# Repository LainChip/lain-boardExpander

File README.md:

# lain-boardExpander

NSCSCC 2023 Lain Core项目SoC使用的拓展板卡。

基于tyh学长的sd拓展板卡，删除了Type-C口，添加01x11排母用于连接PCM5102 I2S DAC。

原理图：

使用工具：KiCad 7.0

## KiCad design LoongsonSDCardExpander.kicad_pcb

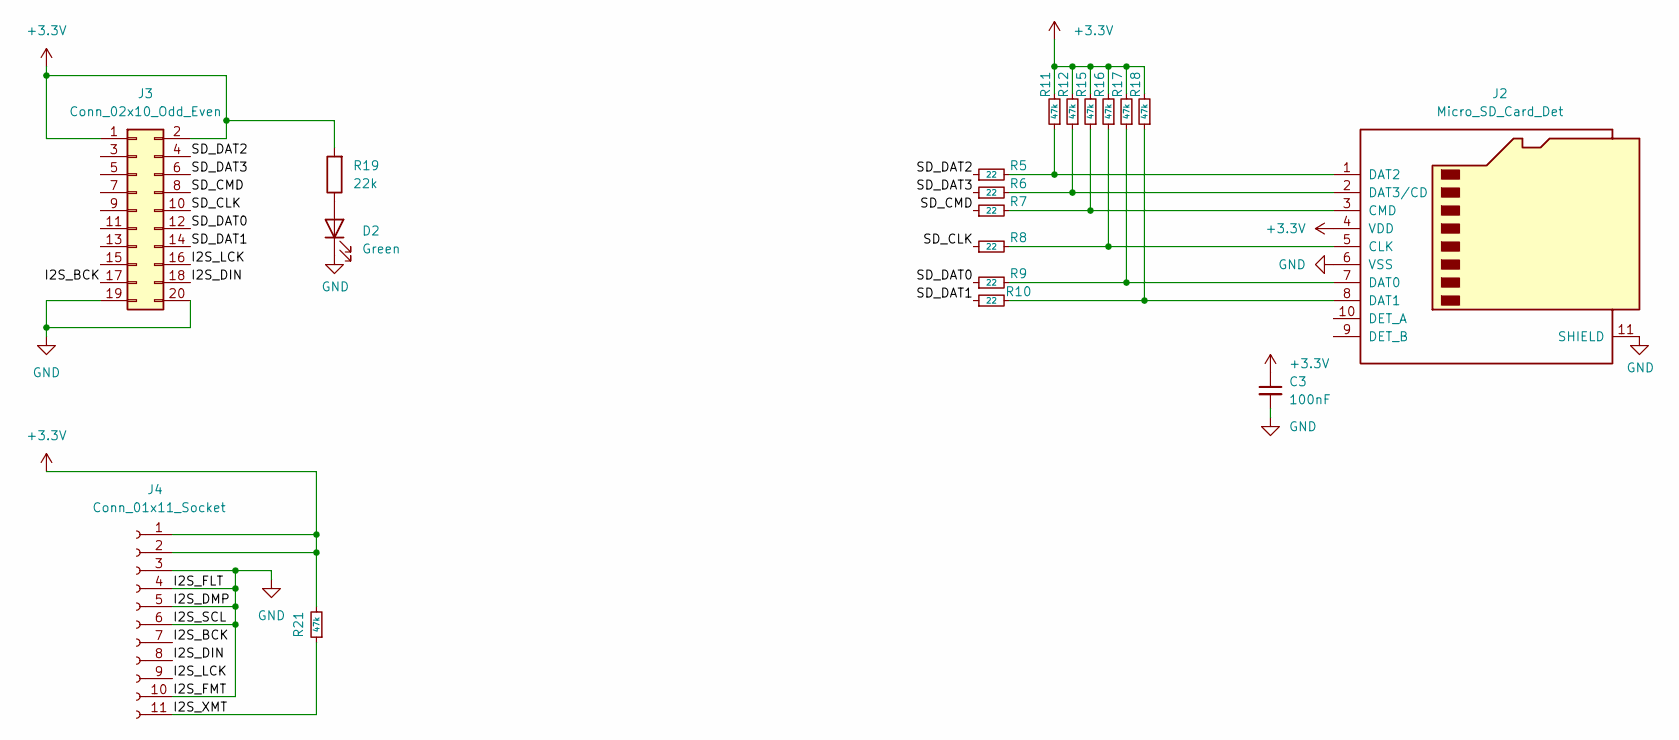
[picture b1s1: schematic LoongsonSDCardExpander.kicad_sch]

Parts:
C3: 100nF; 0402_C
D2: Green; 0805_LED_S1_NUM
J2: Micro_SD_Card_Det; XUNPU-TF-115
J3: Conn_02x10_Odd_Even; PinSocket_2.54mm_Nose
J4: Conn_01x11_Socket; PinSocket_1x11_P2.54mm_Vertical
R5, R6, R7, R8, R9, R10: 22; 0402_R
R11, R12, R15, R16, R17, R18, R21: 47k; 0402_R
R19: 22k; 0402_R

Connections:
+3.3V: C3.1, J2.4 (VDD), J3.1, J3.2, J4.1, J4.2, R11.2, R12.2, R15.2, R16.2, R17.2, R18.2, R19.2, R21.2
/I2S_BCK: J3.17, J4.7
/I2S_DIN: J3.18, J4.8
/I2S_LCK: J3.16, J4.9
/I2S_XMT: J4.11, R21.1
/SD_CLK: J3.10, R8.1
/SD_CMD: J3.8, R7.1
/SD_DAT0: J3.12, R9.1
/SD_DAT1: J3.14, R10.1
/SD_DAT2: J3.4, R5.1
/SD_DAT3: J3.6, R6.1
GND: C3.2, D2.1 (K), J2.6 (VSS), J2.11 (SHIELD), J3.19, J3.20, J4.3, J4.4, J4.5, J4.6, J4.10
unnamed: D2.2 (A), R19.1
unnamed: J2.5 (CLK), R8.2, R16.1
unnamed: J2.3 (CMD), R7.2, R15.1
unnamed: J2.7 (DAT0), R9.2, R17.1
unnamed: J2.8 (DAT1), R10.2, R18.1
unnamed: J2.1 (DAT2), R5.2, R11.1
unnamed: J2.2 (DAT3/CD), R6.2, R12.1

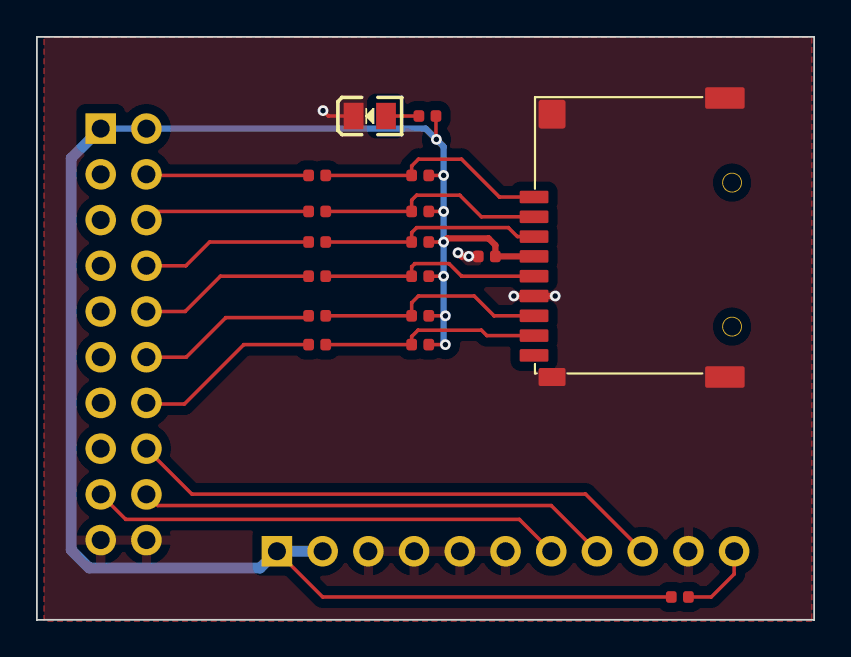
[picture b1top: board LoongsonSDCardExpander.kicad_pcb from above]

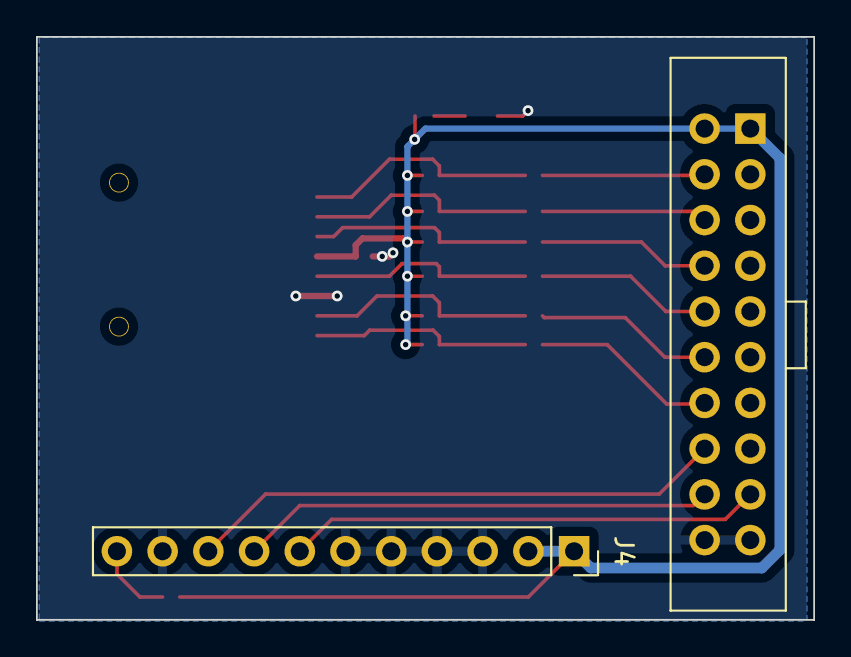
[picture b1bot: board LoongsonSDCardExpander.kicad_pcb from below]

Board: 2 copper layers, 43.2 x 32.4 mm, 19 parts (2 on the bottom side), 19 nets.

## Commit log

2023-08-23 添加Conn_01x11_Socket
